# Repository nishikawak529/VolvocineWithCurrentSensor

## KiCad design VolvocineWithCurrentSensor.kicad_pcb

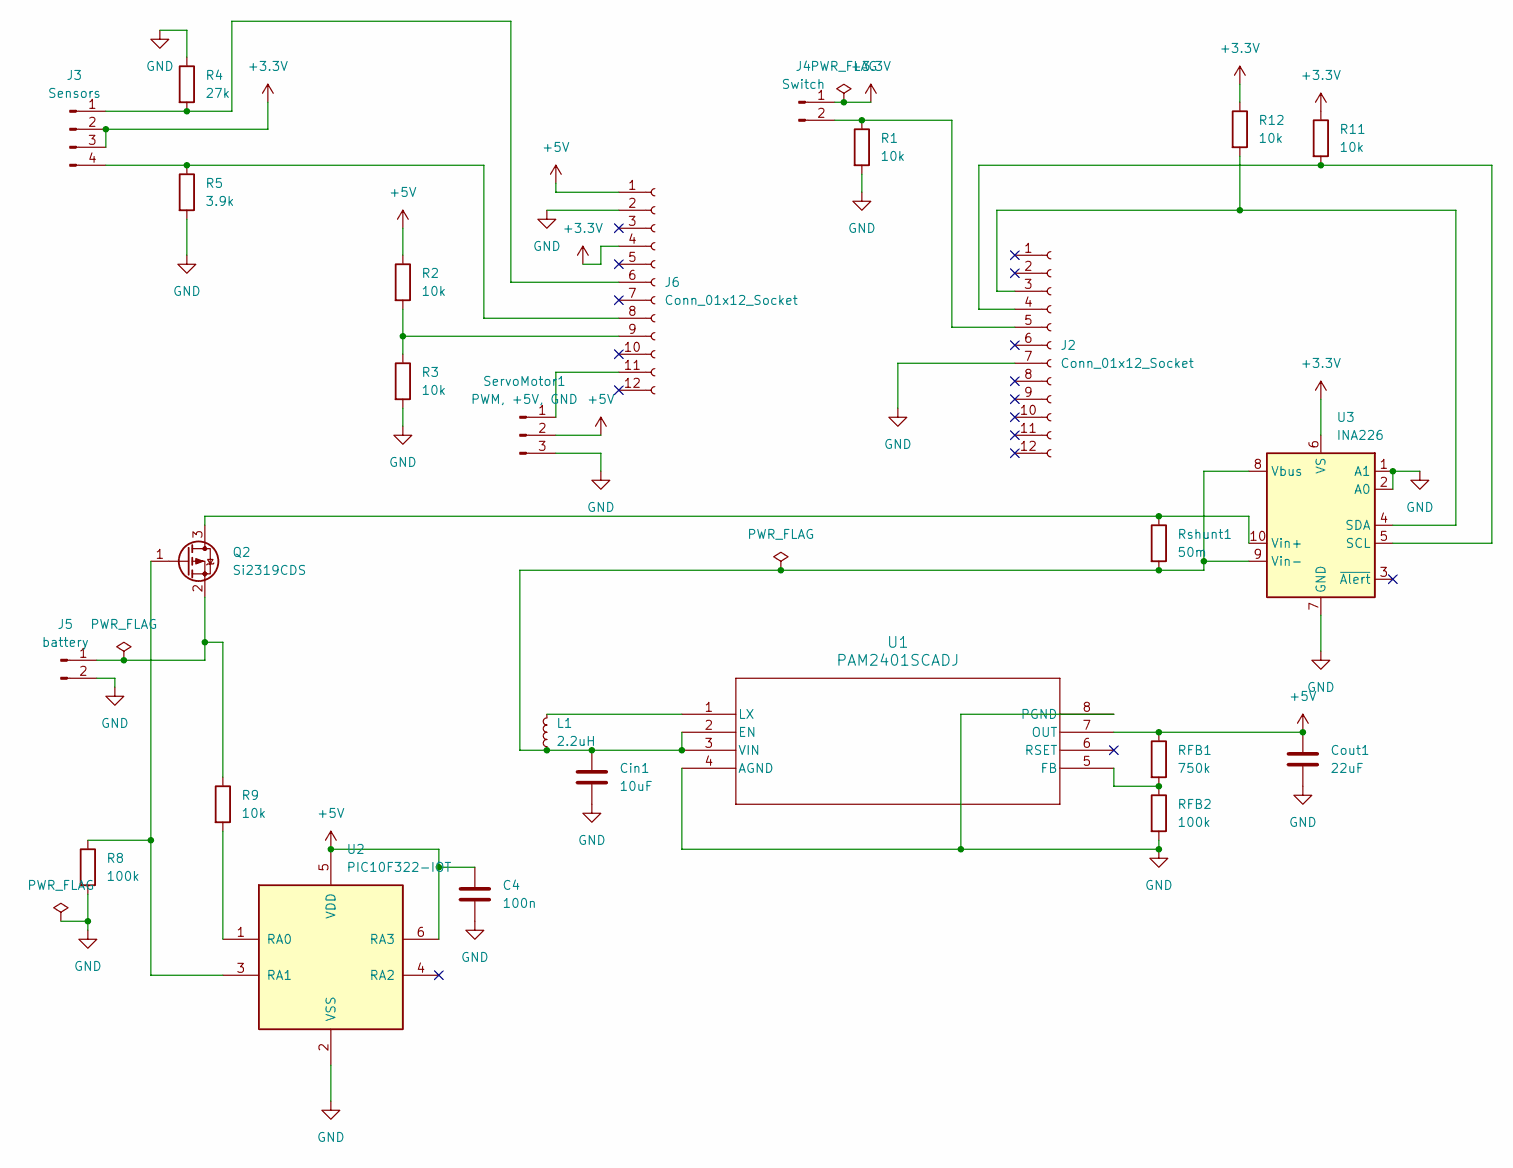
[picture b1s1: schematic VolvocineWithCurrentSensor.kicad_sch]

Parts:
C4: 100n; C_0603_1608Metric_Pad1.08x0.95mm_HandSolder
Cin1: 10uF; C_0603_1608Metric_Pad1.08x0.95mm_HandSolder
Cout1: 22uF; C_1206_3216Metric_Pad1.33x1.80mm_HandSolder
J2, J6: Conn_01x12_Socket; PinSocket_1x12_P2.54mm_Vertical
J3: Sensors; PinHeader_1x04_P2.54mm_Horizontal
J4: Switch; PinHeader_1x02_P2.54mm_Horizontal
J5: battery; PinHeader_1x02_P2.54mm_Horizontal
L1: 2.2uH; L_1008_2520Metric_Pad1.43x2.20mm_HandSolder
Q2: Si2319CDS; SOT-23
R1, R2, R3, R9, R11, R12: 10k; R_0603_1608Metric_Pad0.98x0.95mm_HandSolder
R4: 27k; R_0603_1608Metric_Pad0.98x0.95mm_HandSolder
R5: 3.9k; R_0603_1608Metric_Pad0.98x0.95mm_HandSolder
R8: 100k; R_0603_1608Metric_Pad0.98x0.95mm_HandSolder
RFB1: 750k; R_0603_1608Metric_Pad0.98x0.95mm_HandSolder
RFB2: 100k; R_0603_1608Metric_Pad0.98x0.95mm_HandSolder
Rshunt1: 50m; R_1206_3216Metric_Pad1.30x1.75mm_HandSolder
ServoMotor1: PWM, +5V, GND; PinHeader_1x03_P2.54mm_Horizontal
U1: PAM2401SCADJ; MSOP-8_3x3mm_P0.65mm
U2: PIC10F322-IOT; SOT-23-6
U3: INA226; VSSOP-10_3x3mm_P0.5mm

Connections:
+3.3V: J3.2, J3.3, J4.1, J6.4, R11.1, R12.1, U3.6 (VS)
+5V: C4.1, Cout1.1, J6.1, R2.1, RFB1.1, ServoMotor1.2, U1.7 (OUT), U2.5 (VDD), U2.6 (RA3)
GND: C4.2, Cin1.2, Cout1.2, J2.7, J5.2, J6.2, R1.2, R3.2, R4.1, R5.2, R8.2, RFB2.2, ServoMotor1.3, U1.4 (AGND), U1.8 (PGND), U2.2 (VSS), U3.1 (A1), U3.2 (A0), U3.7 (GND)
unnamed: J2.3, R12.2, U3.4 (SDA)
unnamed: J2.4, R11.2, U3.5 (SCL)
unnamed: J2.5, J4.2, R1.1
unnamed: J3.1, J6.6, R4.2
unnamed: J3.4, J6.8, R5.1
unnamed: J5.1, Q2.2 (S), R9.1
unnamed: J6.9, R2.2, R3.1
unnamed: J6.11, ServoMotor1.1
unnamed: Q2.3 (D), Rshunt1.1, U3.10 (Vin+)
unnamed: Q2.1 (G), R8.1, U2.3 (RA1)
unnamed: Cin1.1, L1.1, Rshunt1.2, U1.2 (EN), U1.3 (VIN), U3.8 (Vbus), U3.9 (Vin-)
unnamed: RFB1.2, RFB2.1, U1.5 (FB)
unnamed: L1.2, U1.1 (LX)
unnamed: R9.2, U2.1 (RA0)

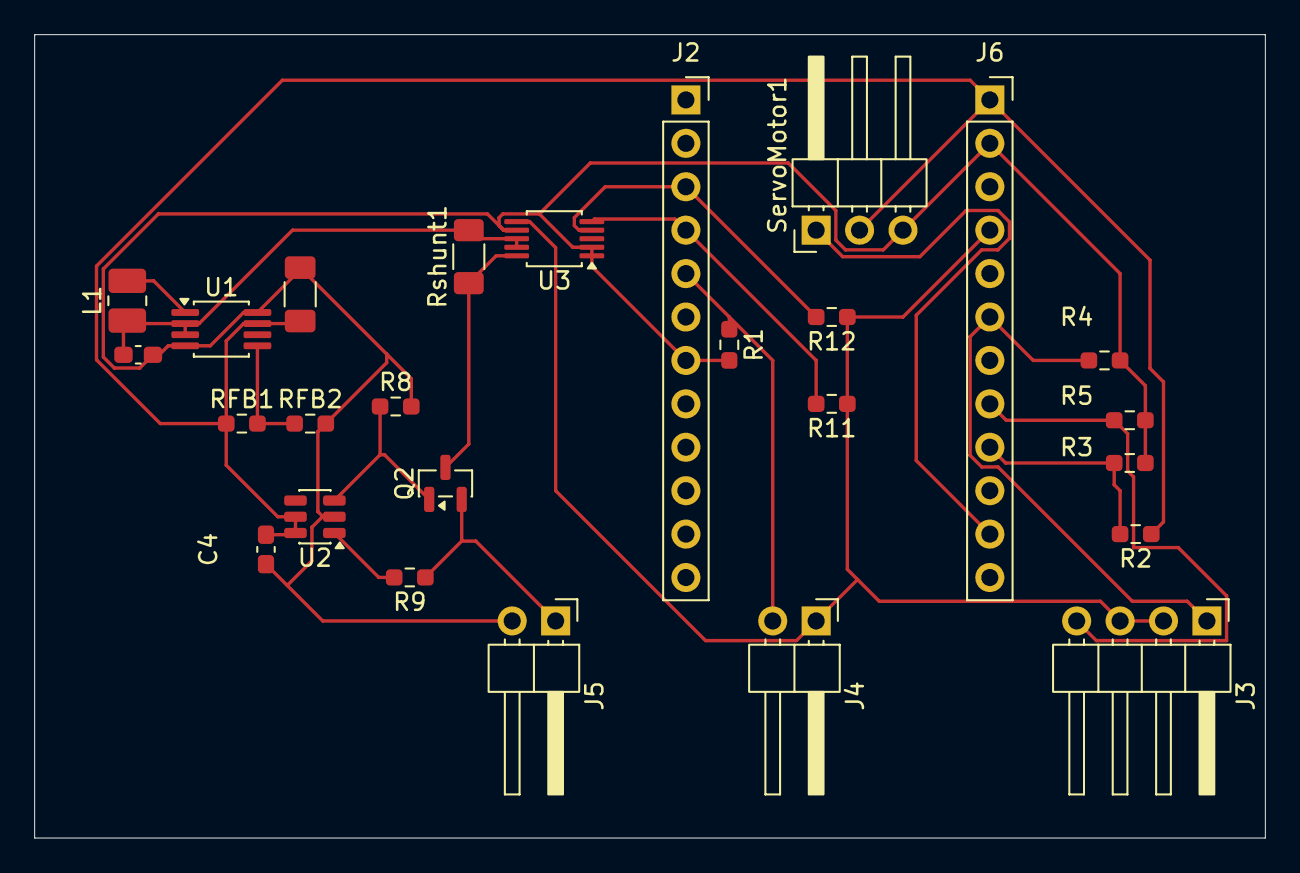
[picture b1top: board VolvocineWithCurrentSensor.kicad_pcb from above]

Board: 2 copper layers, 72.0 x 47.0 mm, 26 parts (0 on the bottom side), 17 nets.

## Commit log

2026-03-02 Remove backups and temporary KiCad files
2026-03-06 Add Gerber and drill files for VolvocineWithCurrentSensor project
    - Created NPTH drill file for non-plated holes.
    - Created PTH drill file for plated through holes with detailed coordinates.
    - Added job file containing project metadata and file attributes for Gerber outputs.
